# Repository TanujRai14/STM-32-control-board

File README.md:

# STM32 Custom Control PCB

## Overview
This repository contains the **hardware and firmware design** for a full-fledged custom PCB based on an **STM32 microcontroller**, developed using **KiCad** for schematic & PCB design and **STM32CubeIDE** for firmware development.

The board is designed for **motor control and communication-heavy applications**, featuring support for **encoders, PWM motor drivers, I²C, UART, CAN**, and robust power and signal routing with extensive via usage and shared planes.

---

## Features

### Microcontroller
- STM32 series microcontroller (configured via STM32CubeMX)
- Optimized pin mapping for peripherals and future expansion
- SWD interface for programming and debugging

### Motor & Encoder Support
- Multiple **PWM outputs** for motor control
- **Quadrature encoder inputs** using hardware timers
- Proper timer and pin allocation to avoid peripheral conflicts

### Communication Interfaces
- **I²C** for sensors and peripherals
- **UART** for debugging, logging, or external modules
- **CAN bus** for robust industrial communication
- All interfaces routed with correct impedance, grounding, and protection considerations

### Power Management
- Dedicated power domains for logic and motor sections
- Decoupling capacitors placed close to MCU power pins
- Proper grounding strategy using shared ground planes
- Bulk capacitance for motor current transients

### PCB Design
- Designed in **KiCad**
- Multi-layer PCB with:
  - Ground and power planes
  - Extensive via stitching for EMI reduction
  - Proper trace width calculation for high-current paths
- Clear separation between noisy (motor) and sensitive (MCU/communication) sections

---

## Repository Structure

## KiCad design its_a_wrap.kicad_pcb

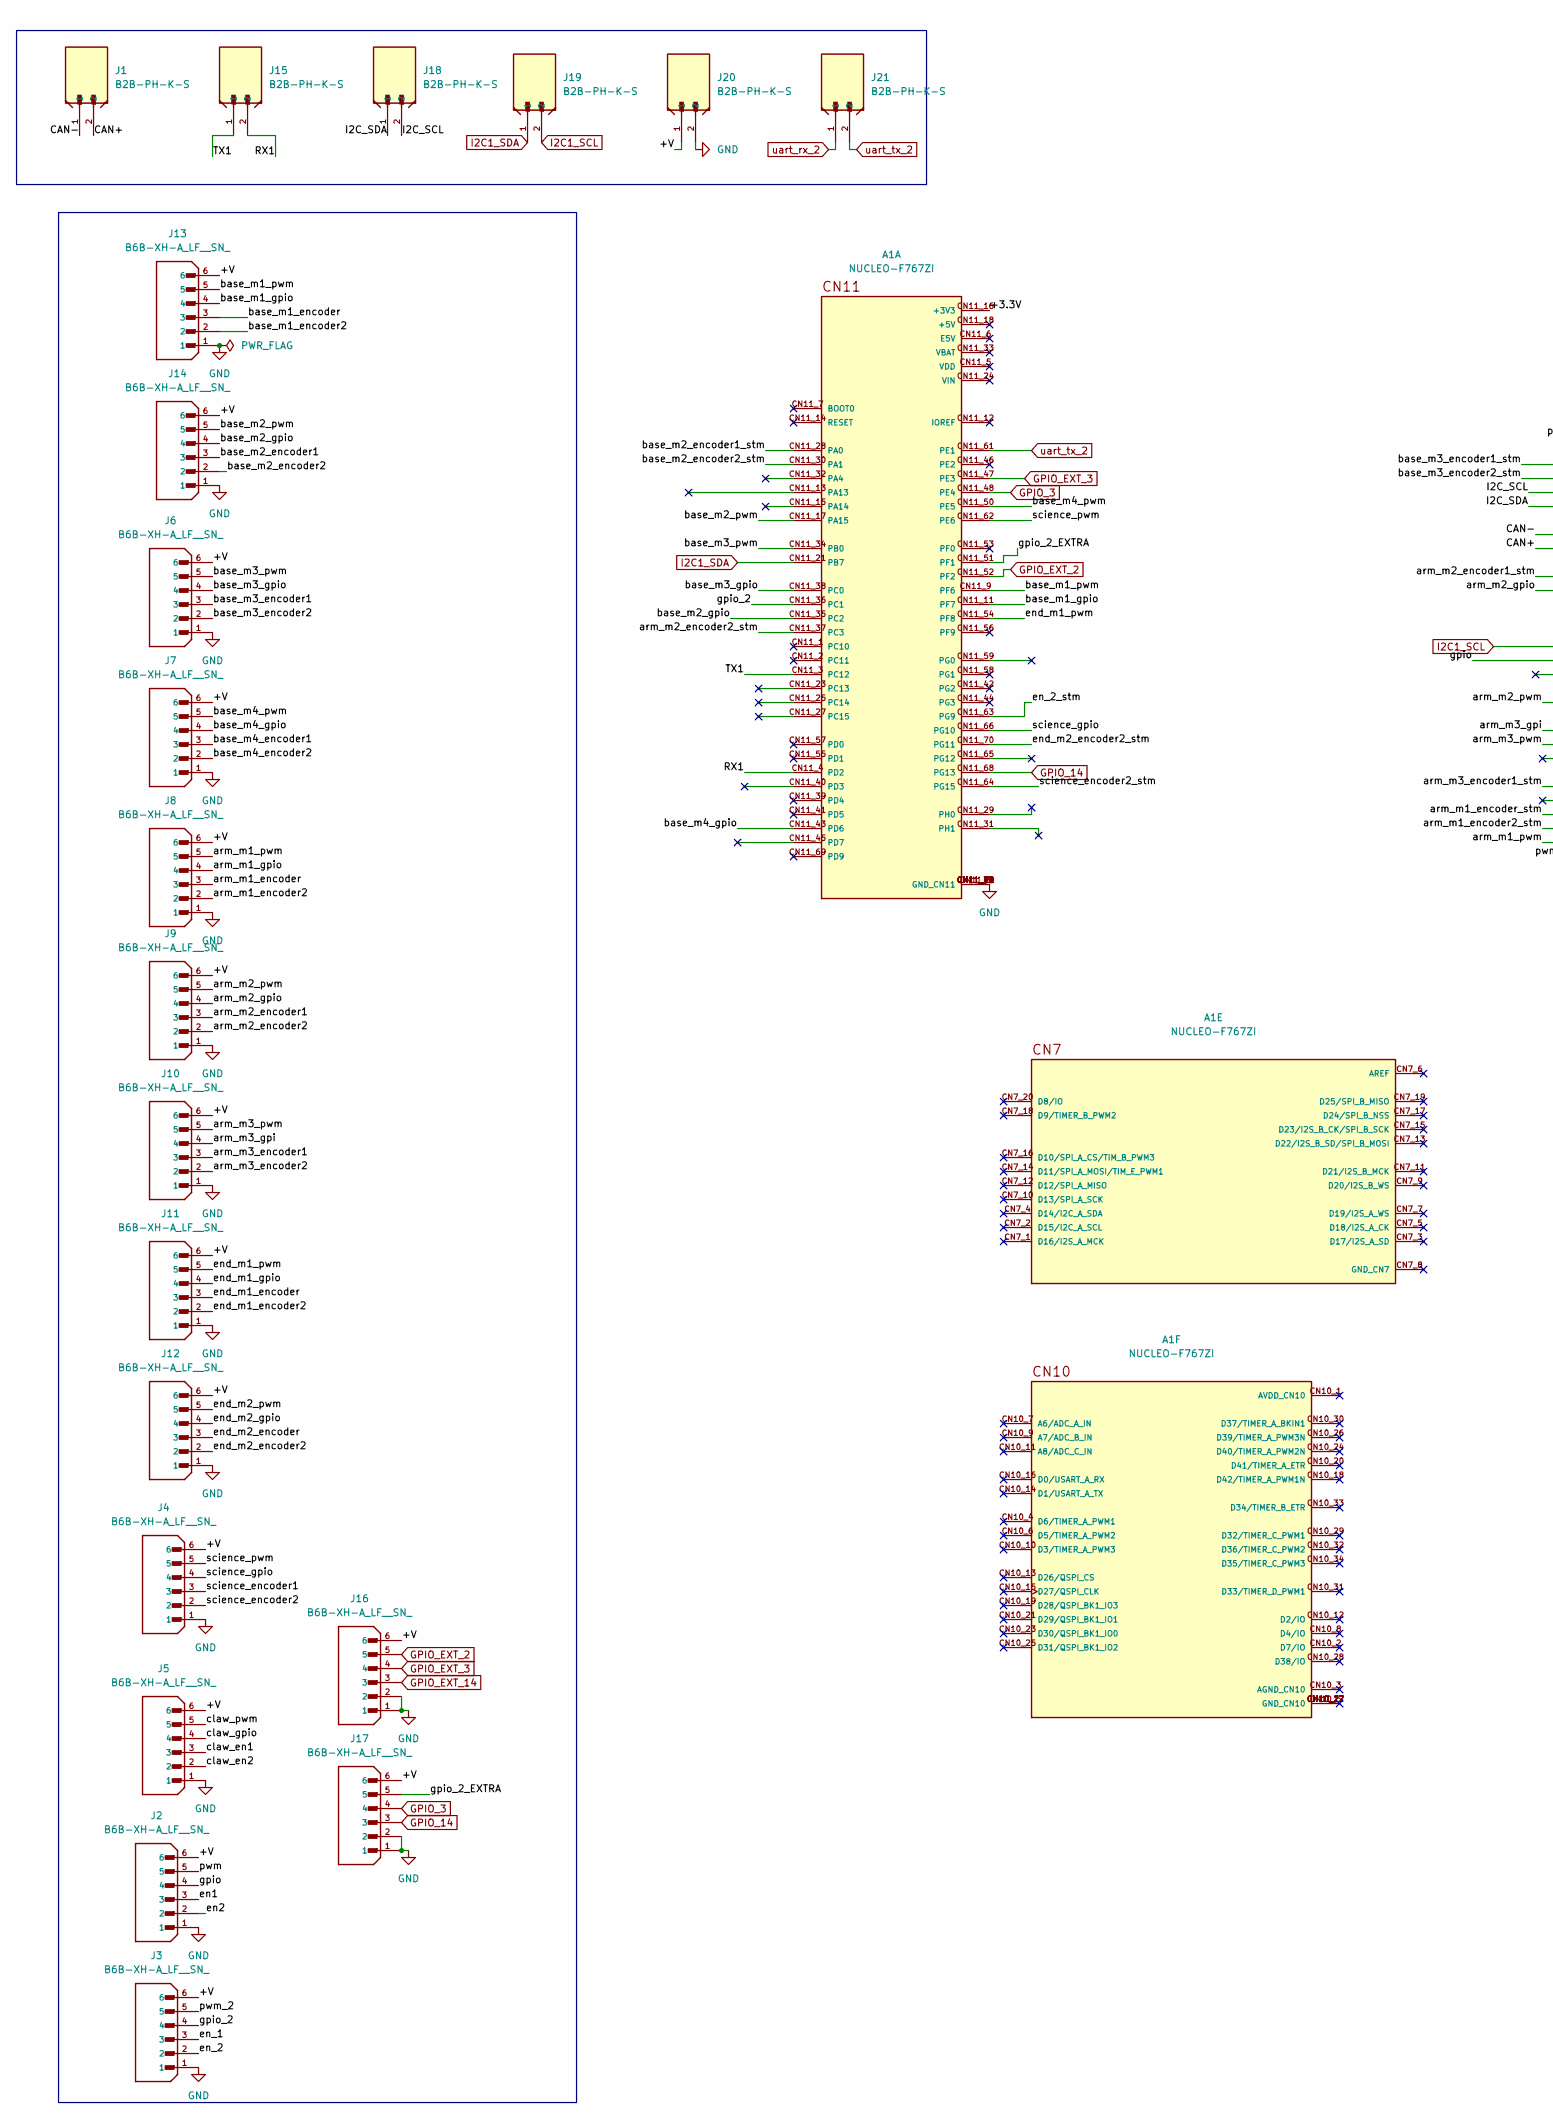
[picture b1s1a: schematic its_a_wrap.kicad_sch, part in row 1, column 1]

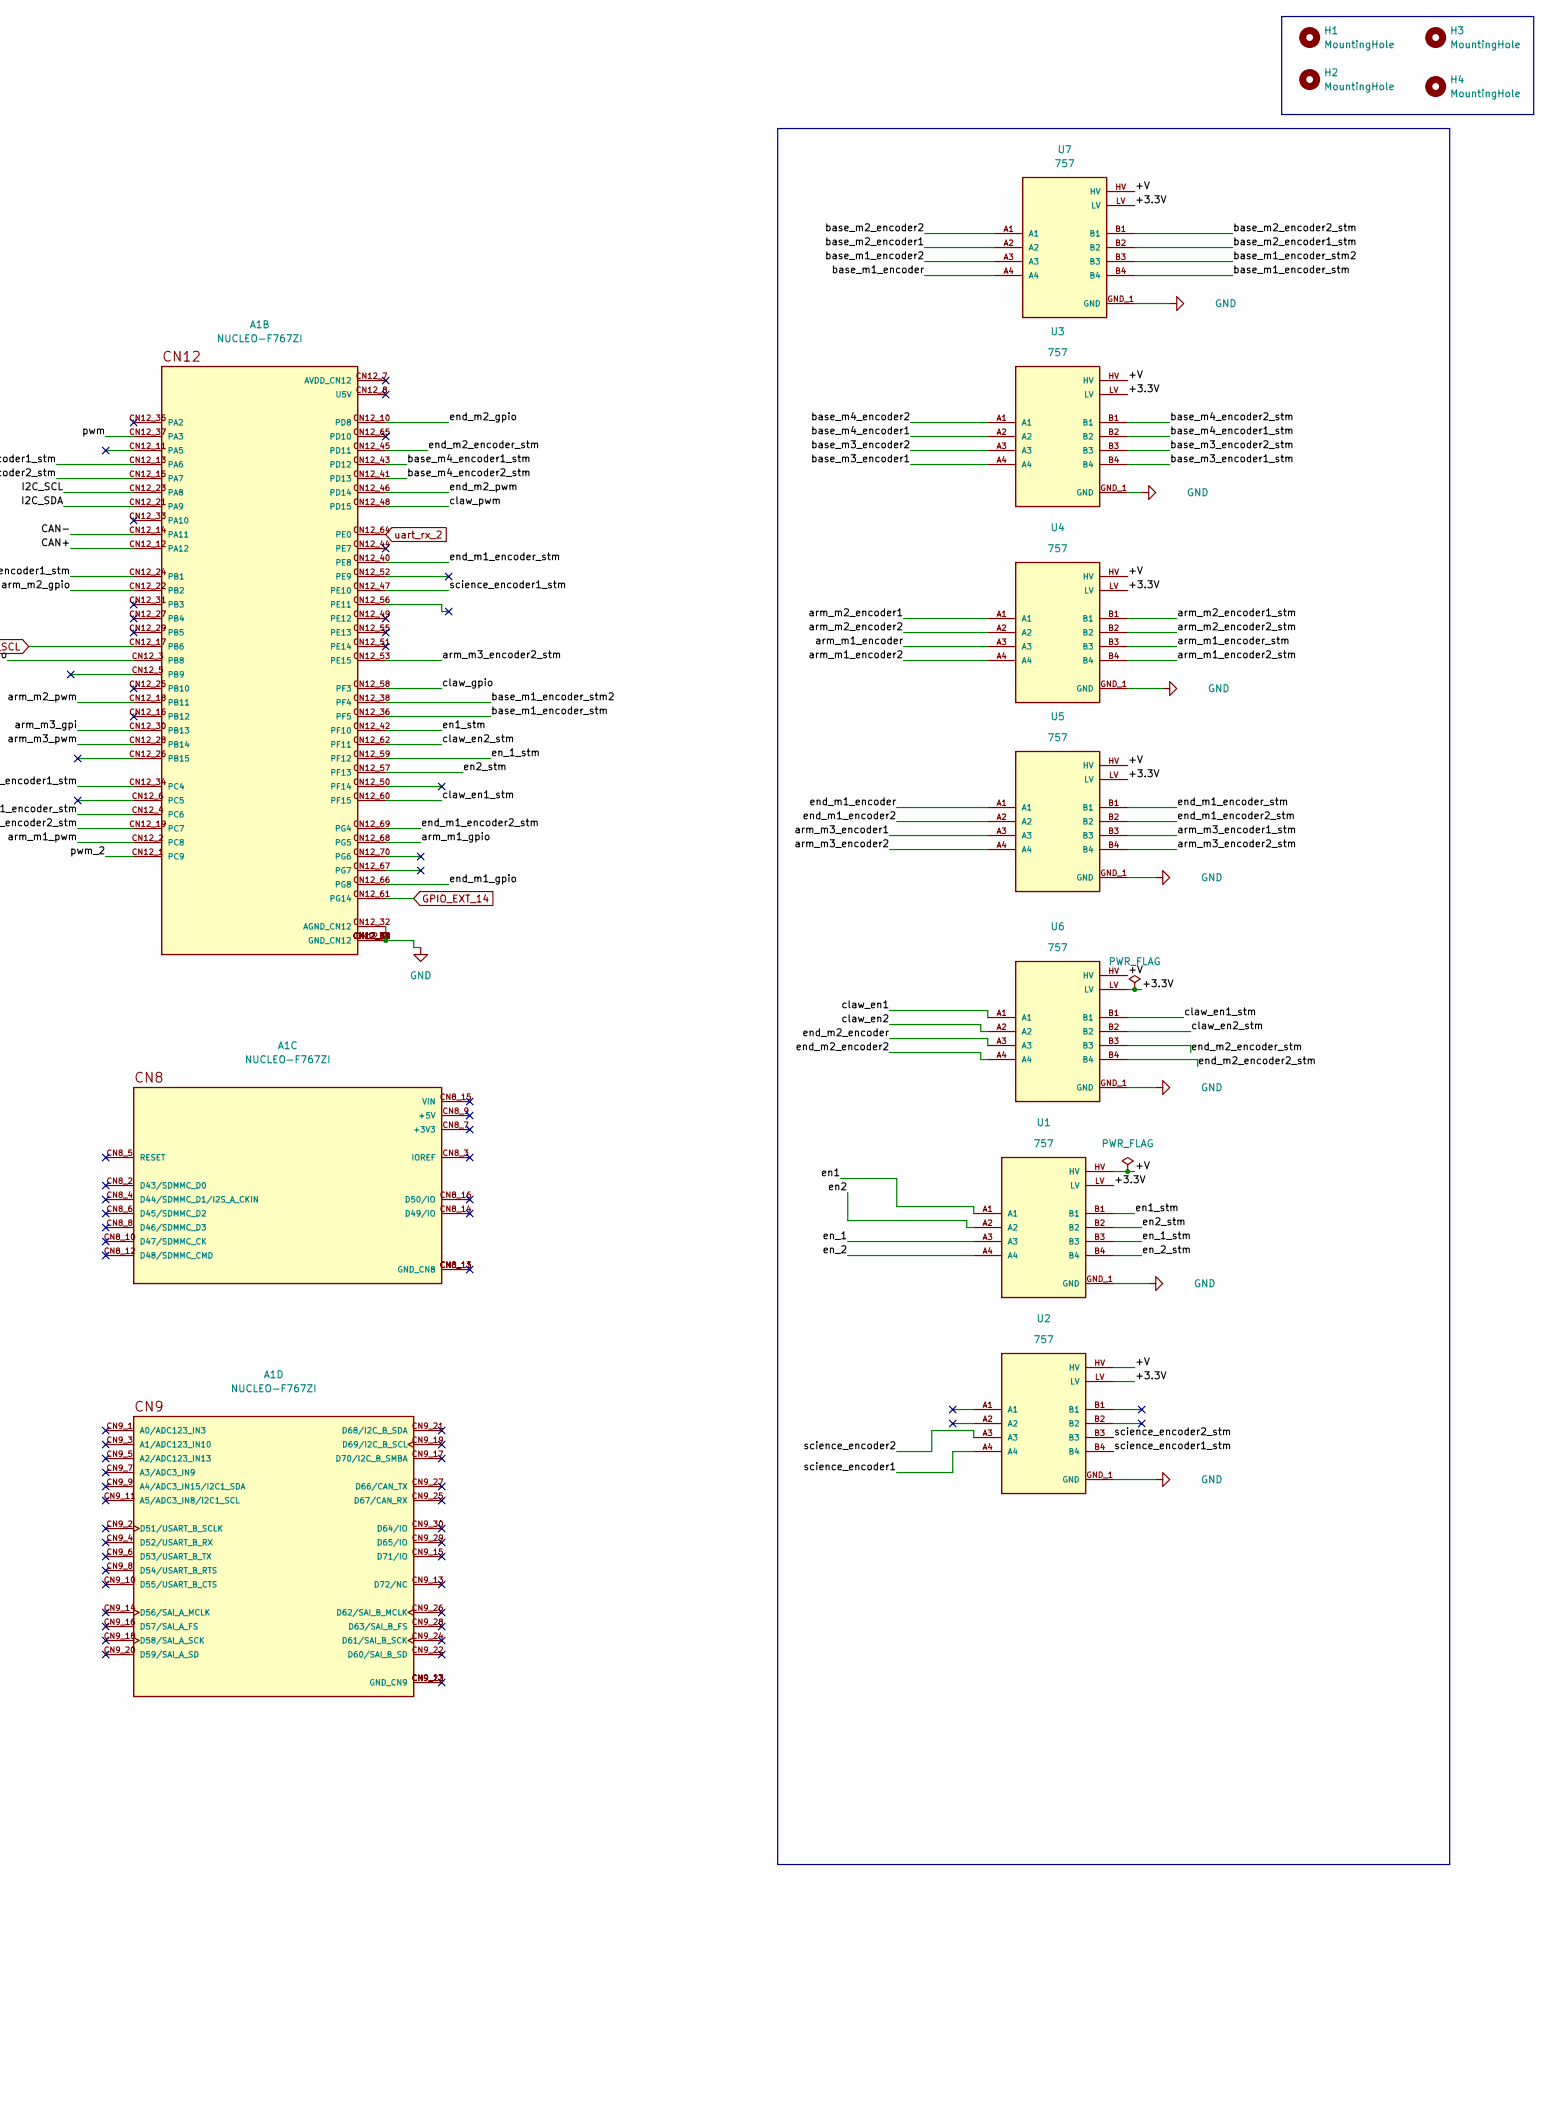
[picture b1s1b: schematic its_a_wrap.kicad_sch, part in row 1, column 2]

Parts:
A1: NUCLEO-F767ZI; ST_NUCLEO-F767ZI; PARTREV 7
H1, H2, H3, H4: MountingHole; MountingHole_3.2mm_M3
J1, J15, J18, J19, J20, J21: B2B-PH-K-S; JST_B2B-PH-K-S
J2, J3, J4, J5, J6, J7, J8, J9, J10, J11, J12, J13, J14, J16, J17: B6B-XH-A_LF__SN_; JST_B6B-XH-A_LF__SN_; PARTREV 7/4/21
U1, U2, U3, U4, U5, U6, U7: 757; MODULE_757; PARTREV N/A

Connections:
/+3.3V: A1.CN11_16 (+3V3), U1.LV, U2.LV, U3.LV, U4.LV, U5.LV, U6.LV, U7.LV
/+V: J2.6, J3.6, J4.6, J5.6, J6.6, J7.6, J8.6, J9.6, J10.6, J11.6, J12.6, J13.6, J14.6, J16.6, J17.6, J20.1, U1.HV, U2.HV, U3.HV, U4.HV, U5.HV, U6.HV, U7.HV
/CAN+: A1.CN12_12 (PA12), J1.2
/CAN-: A1.CN12_14 (PA11), J1.1
/I2C_SCL: A1.CN12_23 (PA8), J18.2
/I2C_SDA: A1.CN12_21 (PA9), J18.1
/RX1: A1.CN11_4 (PD2), J15.2
/TX1: A1.CN11_3 (PC12), J15.1
/arm_m1_encoder: J8.3, U4.A3
/arm_m1_encoder2: J8.2, U4.A4
/arm_m1_encoder2_stm: A1.CN12_19 (PC7), U4.B4
/arm_m1_encoder_stm: A1.CN12_4 (PC6), U4.B3
/arm_m1_gpio: A1.CN12_68 (PG5), J8.4
/arm_m1_pwm: A1.CN12_2 (PC8), J8.5
/arm_m2_encoder1: J9.3, U4.A1
/arm_m2_encoder1_stm: A1.CN12_24 (PB1), U4.B1
/arm_m2_encoder2: J9.2, U4.A2
/arm_m2_encoder2_stm: A1.CN11_37 (PC3), U4.B2
/arm_m2_gpio: A1.CN12_22 (PB2), J9.4
/arm_m2_pwm: A1.CN12_18 (PB11), J9.5
/arm_m3_encoder1: J10.3, U5.A3
/arm_m3_encoder1_stm: A1.CN12_34 (PC4), U5.B3
/arm_m3_encoder2: J10.2, U5.A4
/arm_m3_encoder2_stm: A1.CN12_53 (PE15), U5.B4
/arm_m3_gpi: A1.CN12_30 (PB13), J10.4
/arm_m3_pwm: A1.CN12_28 (PB14), J10.5
/base_m1_encoder: J13.3, U7.A4
/base_m1_encoder2: J13.2, U7.A3
/base_m1_encoder_stm: A1.CN12_36 (PF5), U7.B4
/base_m1_encoder_stm2: A1.CN12_38 (PF4), U7.B3
/base_m1_gpio: A1.CN11_11 (PF7), J13.4
/base_m1_pwm: A1.CN11_9 (PF6), J13.5
/base_m2_encoder1: J14.3, U7.A2
/base_m2_encoder1_stm: A1.CN11_28 (PA0), U7.B2
/base_m2_encoder2: J14.2, U7.A1
/base_m2_encoder2_stm: A1.CN11_30 (PA1), U7.B1
/base_m2_gpio: A1.CN11_35 (PC2), J14.4
/base_m2_pwm: A1.CN11_17 (PA15), J14.5
/base_m3_encoder1: J6.3, U3.A4
/base_m3_encoder1_stm: A1.CN12_13 (PA6), U3.B4
/base_m3_encoder2: J6.2, U3.A3
/base_m3_encoder2_stm: A1.CN12_15 (PA7), U3.B3
/base_m3_gpio: A1.CN11_38 (PC0), J6.4
/base_m3_pwm: A1.CN11_34 (PB0), J6.5
/base_m4_encoder1: J7.3, U3.A2
/base_m4_encoder1_stm: A1.CN12_43 (PD12), U3.B2
/base_m4_encoder2: J7.2, U3.A1
/base_m4_encoder2_stm: A1.CN12_41 (PD13), U3.B1
/base_m4_gpio: A1.CN11_43 (PD6), J7.4
/base_m4_pwm: A1.CN11_50 (PE5), J7.5
/claw_en1: J5.3, U6.A1
/claw_en1_stm: A1.CN12_60 (PF15), U6.B1
/claw_en2: J5.2, U6.A2
/claw_en2_stm: A1.CN12_62 (PF11), U6.B2
/claw_gpio: A1.CN12_58 (PF3), J5.4
/claw_pwm: A1.CN12_48 (PD15), J5.5
/en1: J2.3, U1.A1
/en1_stm: A1.CN12_42 (PF10), U1.B1
/en2: J2.2, U1.A2
/en2_stm: A1.CN12_57 (PF13), U1.B2
/en_1: J3.3, U1.A3
/en_1_stm: A1.CN12_59 (PF12), U1.B3
/en_2: J3.2, U1.A4
/en_2_stm: A1.CN11_63 (PG9), U1.B4
/end_m1_encoder: J11.3, U5.A1
/end_m1_encoder2: J11.2, U5.A2
/end_m1_encoder2_stm: A1.CN12_69 (PG4), U5.B2
/end_m1_encoder_stm: A1.CN12_40 (PE8), U5.B1
/end_m1_gpio: A1.CN12_66 (PG8), J11.4
/end_m1_pwm: A1.CN11_54 (PF8), J11.5
/end_m2_encoder: J12.3, U6.A3
/end_m2_encoder2: J12.2, U6.A4
/end_m2_encoder2_stm: A1.CN11_70 (PG11), U6.B4
/end_m2_encoder_stm: A1.CN12_45 (PD11), U6.B3
/end_m2_gpio: A1.CN12_10 (PD8), J12.4
/end_m2_pwm: A1.CN12_46 (PD14), J12.5
/gpio: A1.CN12_3 (PB8), J2.4
/gpio_2: A1.CN11_36 (PC1), J3.4
/gpio_2_EXTRA: A1.CN11_51 (PF1), J17.5
/pwm: A1.CN12_37 (PA3), J2.5
/pwm_2: A1.CN12_1 (PC9), J3.5
/science_encoder1: J4.3, U2.A4
/science_encoder1_stm: A1.CN12_47 (PE10), U2.B4
/science_encoder2: J4.2, U2.A3
/science_encoder2_stm: A1.CN11_64 (PG15), U2.B3
/science_gpio: A1.CN11_66 (PG10), J4.4
/science_pwm: A1.CN11_62 (PE6), J4.5
GND: A1.CN11_8 (GND_CN11), A1.CN11_19 (GND_CN11), A1.CN11_20 (GND_CN11), A1.CN11_22 (GND_CN11), A1.CN11_49 (GND_CN11), A1.CN11_60 (GND_CN11), A1.CN11_71 (GND_CN11), A1.CN11_72 (GND_CN11), A1.CN12_9 (GND_CN12), A1.CN12_20 (GND_CN12), A1.CN12_32 (AGND_CN12), A1.CN12_39 (GND_CN12), A1.CN12_54 (GND_CN12), A1.CN12_63 (GND_CN12), A1.CN12_71 (GND_CN12), A1.CN12_72 (GND_CN12), J2.1, J3.1, J4.1, J5.1, J6.1, J7.1, J8.1, J9.1, J10.1, J11.1, J12.1, J13.1, J14.1, J16.1, J16.2, J17.1, J17.2, J20.2, U1.GND_1 (GND), U1.GND_2 (GND), U2.GND_1 (GND), U2.GND_2 (GND), U3.GND_1 (GND), U3.GND_2 (GND), U4.GND_1 (GND), U4.GND_2 (GND), U5.GND_1 (GND), U5.GND_2 (GND), U6.GND_1 (GND), U6.GND_2 (GND), U7.GND_1 (GND), U7.GND_2 (GND)
GPIO_3: A1.CN11_48 (PE4), J17.4
GPIO_14: A1.CN11_68 (PG13), J17.3
GPIO_EXT_2: A1.CN11_52 (PF2), J16.5
GPIO_EXT_3: A1.CN11_47 (PE3), J16.4
GPIO_EXT_14: A1.CN12_61 (PG14), J16.3
I2C1_SCL: A1.CN12_17 (PB6), J19.2
I2C1_SDA: A1.CN11_21 (PB7), J19.1
uart_rx_2: A1.CN12_64 (PE0), J21.1
uart_tx_2: A1.CN11_61 (PE1), J21.2

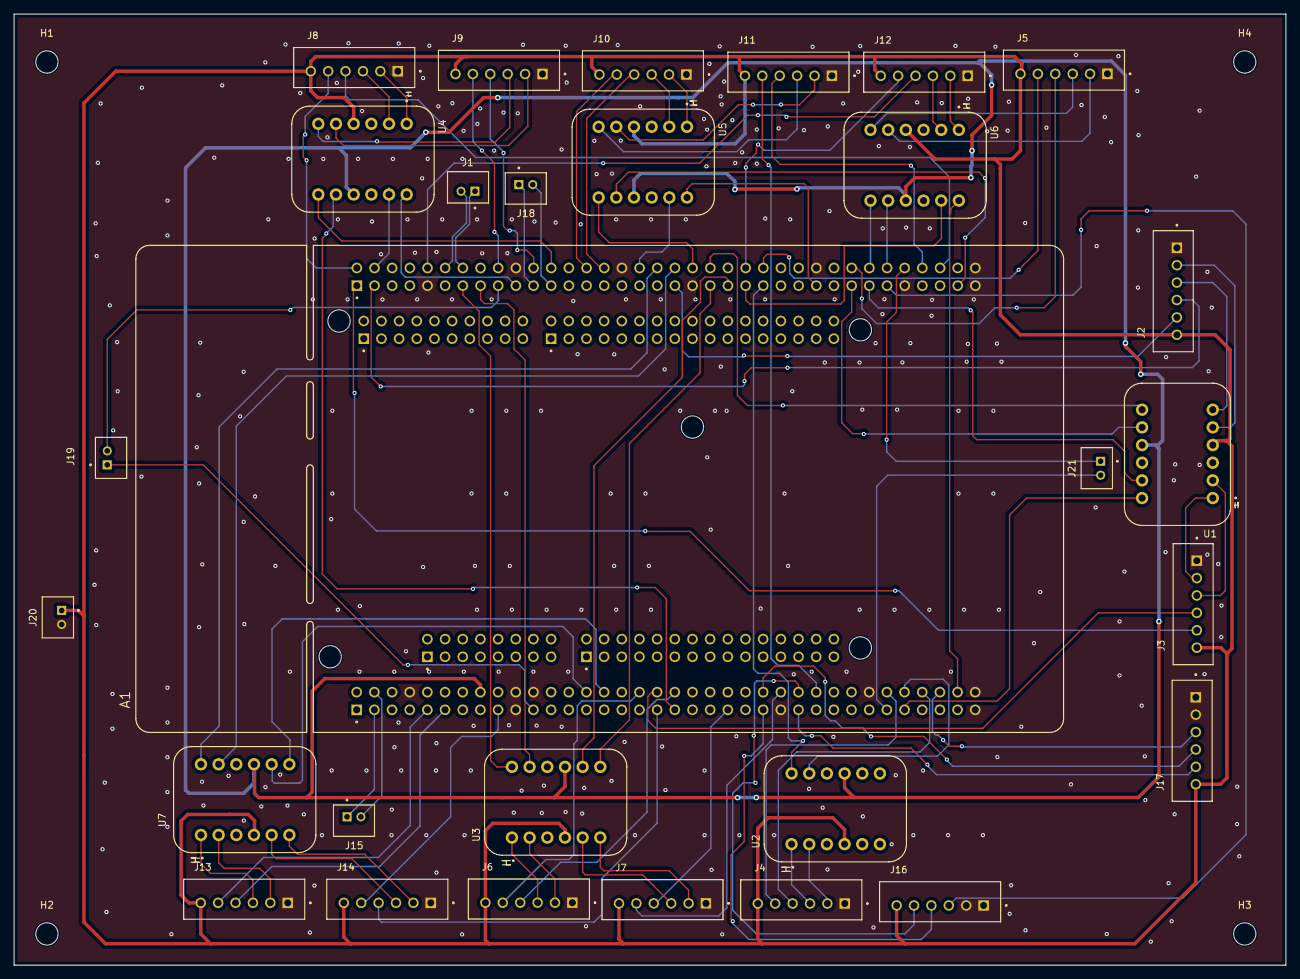
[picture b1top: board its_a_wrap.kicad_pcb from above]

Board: 2 copper layers, 182.8 x 136.7 mm, 33 parts (0 on the bottom side), 97 nets.

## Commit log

2026-02-10 Revise README with project details and features
    Updated project title and added detailed overview and features sections for the STM32 custom control PCB.
